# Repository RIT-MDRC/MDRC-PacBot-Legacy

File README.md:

# MDRC-PacBot
RIT MDRC's robot competing in Harvard's Pacbot Competition.

## Hardware

# What you need

1. A Raspberry Pi 4b
2. An Arduino Uno
3. A USB-B to USB-A adapter
4. Adafruit Motor Shield v2
5. USC-C to USB-A cable for powering the Raspberry Pi
6. 5 distance sensors (Sharp 0A51SK F 02)
7. The Pacbot shell
8. Motors (2x DC motors, 30:1 Micro Metal Gearmotor LP 6V with Extended Motor Shaft (Item #2202))
9. 2 Wheels
10. 1 caster wheel
11. Code from MDRC pacbot repo (https://github.com/RIT-MDRC/MDRC-PacBot.git)

# How to build the robot

1. Put the distance sensors in the holes of the Pacbot shell.
2. Plug the motor shield into the Arduino.
3. Ensure the microSD card is inserted into the Raspberry Pi.
4. Plug the raspberry pi into a power source using the USB-C to A cord.
5. Plug the arduino into the Raspberry Pi using the USB-A to USB-B cable.
6. Plug the motors into the motor shield using the M1 and M2 slots.
7. Plug the power wires of the sensors (red + black) into the 5v power of the motor shield
8. Plug the data wire (white) into the analog input of the motor shield.
9. Put the wheels on the motor axles.
10. Plug the 9V battery into the motor shield using the 5-12V wire slots.
11. SSH into the raspberry pi: `ssh pi@mdrcpi4.student.rit.edu`
12. Run ls /dev/tty* to find the serial port of the Arduino (similar to "USB0").
13. Locate motorControllerPassthrough.py and run it on the Raspberry Pi with the argument of /dev/tty/USB0 (replace with serial port).
14. On your computer, locate motorControllerPassthroughClient.py and run it: `python3 motorControllerPassthroughClient.py ws://mdrcpi4.student.rit.edu:8765`
15. Type "f", "b", "l", "r", or "s" (stop) to control the robot, or "q" to quit the program.

To learn more about the software, see the doc in the MDRC google drive https://docs.google.com/document/d/10UM2JkGd73kfUx4oTEAEH53nK31bbPSw4fjkly4F9ZI/edit

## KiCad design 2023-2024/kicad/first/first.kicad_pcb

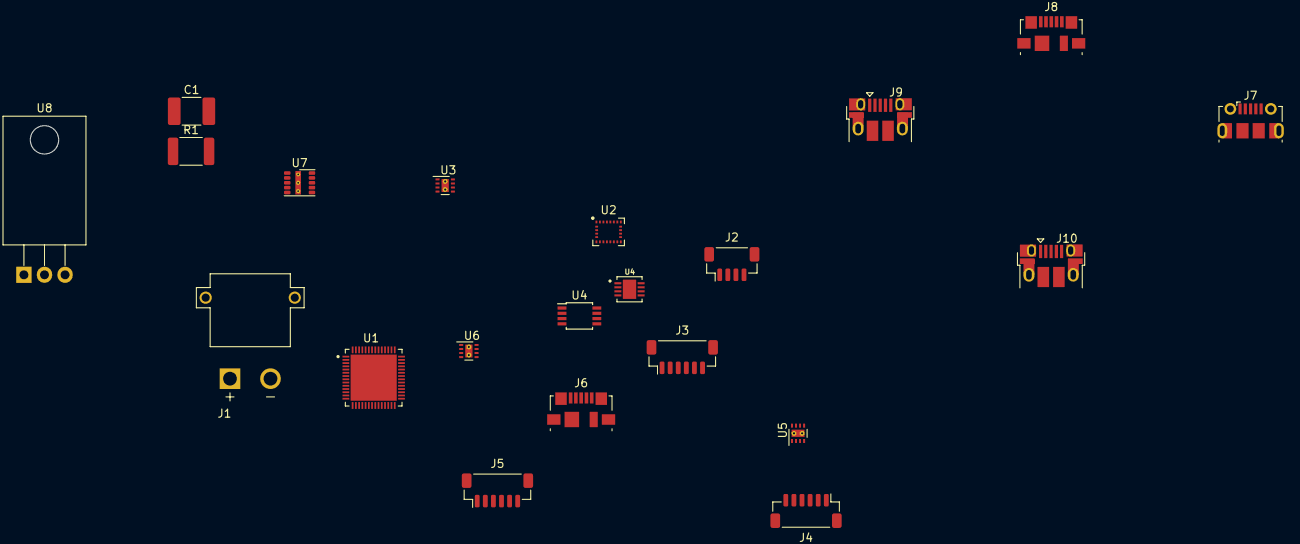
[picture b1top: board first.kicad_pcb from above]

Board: 2 copper layers, 21 parts (0 on the bottom side), 13 nets, no tracks yet.

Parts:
C1: 1u; C_1812_4532Metric_Pad1.57x3.40mm_HandSolder
J1: XT30PW-M; AMASS_XT30PW-M
J2: Conn_01x04; JST_SH_BM04B-SRSS-TB_1x04-1MP_P1.00mm_Vertical
J3, J4, J5: Conn_01x06; JST_SH_BM06B-SRSS-TB_1x06-1MP_P1.00mm_Vertical
J6, J8: USB_B_Micro; USB_Micro-B_Molex_47346-0001
J7: USB_B_Micro; USB_Micro-B_Molex-105017-0001
J9, J10: USB_B_Micro; USB_Micro-B_Amphenol_10103594-0001LF_Horizontal
R1: 50m; R_1812_4532Metric_Pad1.30x3.40mm_HandSolder
U1: ESP32-S3FH4R2; QFN40P700X700X90-57N
U2: LSM9DS1; LGA-24L_3x3.5mm_P0.43mm
U3, U5, U6: DRV8212P; WSON-8-1EP_2x2mm_P0.5mm_EP0.9x1.6mm_ThermalVias
U4: LTC2943IDD_PBF; SON50P300X300X80-9N
U4#2: DS2745U; TSSOP-8_3x3mm_P0.65mm
U7: LMZM23601V3; Texas_SIL0010A_MicroSiP-10-1EP_3.8x3mm_P0.6mm_EP0.7x2.9mm_T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
U8: LM7806_TO220; TO-220-3_Horizontal_TabDown

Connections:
+3.3V: J2.3, J3.3, J4.3, J5.3, U2.1 (VDDIO), U2.3 (VDDIO), U2.22 (VDD), U2.23 (VDD), U3.8 (VCC), U5.8 (VCC), U6.8 (VCC), U7.6 (VOUT), U7.7 (FB)
+6V: U3.1 (VM), U5.1 (VM), U6.1 (VM), U7.3 (VIN), U7.4 (EN), U8.3 (VO)
GND: C1.1, J1.N, J2.4, J3.6, J4.6, J5.6, J6.5 (GND), U1.57 (GND), U2.19 (GND), U2.20 (GND), U3.4 (GND), U3.9 (GND), U4.2 (GND), U4.3 (GND), U4.7 (GND), U4.9 (EXP), U5.4 (GND), U5.9 (GND), U6.4 (GND), U6.9 (GND), U7.1 (GND), U7.11 (GND), U8.2 (GND)
unnamed: J3.1, U6.2 (OUT1)
unnamed: J3.2, U6.3 (OUT2)
unnamed: J4.1, U5.2 (OUT1)
unnamed: J4.2, U5.3 (OUT2)
unnamed: J5.1, U3.2 (OUT1)
unnamed: J5.2, U3.3 (OUT2)
unnamed: U1.2 (VDD3P3), U1.3 (VDD3P3)
unnamed: U1.55 (VDDA), U1.56 (VDDA)
unnamed: C1.2, R1.1, U4.1 (SENSE+), U8.1 (VI)
unnamed: J1.P, R1.2, U4.8 (SENSE-)

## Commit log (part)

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2019-01-29 Meeting update
2019-01-29 addition of a subscription to fullstate into pacneat
2019-02-09 Pacneat can now restart and run the game still errors though
2019-02-12 changed hard
2019-02-23 cleaned up protoAI
2019-03-18 direction
2019-03-19 Changed the address of the highlevelpacman and pacbotcommsmodule using the pis ip address to talk to appear to the server.
2019-03-23 Using RPI
2019-03-23 4 GPIO output config
2019-03-23 Bug fix
2019-03-26 Sensor usage
2019-03-30 PID installation and usage
2019-03-30 ATUNE fix
2019-03-30 goes straight
2019-03-31 more changes
2019-04-03 Initial test of gyro+sensor to turn
2019-04-04 fixed warnings
2019-04-05 changed pins
2019-04-06 small change
2019-04-06 Failsafe randome function works
2019-09-22 Add .gitignore for __pycache__/ and .vscode/ directories
2019-09-23 Stop using the Queue wrapper for collections.deque
    I profiled this, and the Queue wrapper was introducing
    measurable overhead. It's a bit faster just using an
    unwrapped collections.deque.
    I also did some minor, non-functional reformatting.
2019-09-24 Refactor findPath and breadth_first_search control flow
    Use a loop instead of recursion. This is a little faster and
    (in my opinion) more readable.
2019-09-28 Write new optimized_search module
    It uses a precomputed lookup table of distances & directions
    between intersections for very fast distance/direction lookup
    between any two tiles.
    The file preprocess_grid.py generates the lookup tables.
2019-09-28 Comment out GPIO stuff
    So it runs on my laptop
2019-09-28 Print some debug/timing information each tick
2019-09-28 Update find_closest_ghosts to use the new optimized search
2019-09-28 Add .DS_store to the .gitignore
2019-09-28 copied update from 2018
2019-09-28 Created lowlevel folder
2019-10-08 Added headers for lowlevel modules
2020-01-30 -Add logic for motor controller
    -Create wrapper for distance sensor
2020-02-10 Fix some semantic errors
2021-09-19 Changed IP addresses to localhost, added two shell files for use when running on Linux
2021-09-19 Added gitpull.sh to /2021-2022/linux to make it faster to pull to the raspian systems
2021-09-25 + Print the score at each tick
2021-09-25 + Added intermediary print statement for time complexity analysis
2021-09-25 + Fixed directories in pacbotNoVisToFile.sh
2021-09-25 + Added .gitignore to ignore test results + Added line in pacbotNoVisToFile.sh to make the test directory if it doesn't exist
2021-09-25 changed sleep duration from 1 to 0.6s
2021-09-25 changed sleep duration back to 1 second
2021-10-02 + Edited pacbotNoVisToFile.sh to actually start the simulation - it works now as a bash file
2021-10-02 + New sh file path in testweights.py / sleep 5 in testweights.sh to see errors
2021-10-02 channgef heursitic to 1 for super pellsts
2021-10-02 + Fixed file path in testweights.py (again)
2021-10-02 Added a text file that contains the weights of our code used to test for the best combination
2021-10-02 added .split to line 29
2021-10-02 Added loop to read lines in test_weights.txt
2021-10-02 type casted to int on lines 30-35
2021-10-02 Changed frquency to 2 in weighs.txt
2021-10-11 Updates test_weights.txt to match weights.txt, updated testweights.py to use subprocess.Popen instead of subprocess.call because Popen can accept stdin and use stdout
2021-10-11 Updates test_weights.txt to add more iterations, updated testweights.py to kill process when it says "stop" (when pacbot dies) and print out the score for each iteration
2021-10-11 pacbotNoVisToFile.sh now again puts GameEngine output to file, but python script is switched to pacbotNoVis to capture all stdout testweights.py includes a check so that it does not try to do empty l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
2021-10-11 Uses terminate instead of kill, converts binary string using decode
2021-10-11 Forced input to pacbotNoVis.sh
2021-10-11 Fixed command not in list form
2021-10-11 List form command
2021-10-11 Print output from program
2021-10-11 testweights.py now starts all other python processes without the use of the sh file. js file was deleted because this os cannot run node
2021-10-11 Reformat game engine initialization
2021-10-11 Added processes created print and ignored gameEngine output
2021-10-11 Terminate instead of kill
2021-10-11 Print score as int, do all iterations
2021-10-11 Only 1 weights set, also output results to git ignored file
2021-10-11 Added second weights set
2021-10-11 Run only the first iteration - next ones will be run in subsequent processes so that the ports can be released
2021-10-11 Script starts new independent process when finished so that ports can be reopened
2021-10-11 Prints which weight set it is on
2021-10-11 Program waits for Pacman to die before quitting each iteration
2021-10-11 Changed conflicting variable names
2021-10-11 Fixed while loop
2021-10-11 Looking for multiple consecutive stops because sometimes pacman stops on his own
2021-10-13 Made pacbot process nohup in hopes of remerging testweights into single process
2021-10-14 Kill didn't work either, reverting last two commits (terminate instead of kill, no nohup for pacbot progress).
2021-10-14 Fixed shV2 file, removed wait time at the beginning of python script
2021-10-14 Fixed file path when checking if process complete
2021-10-14 Removed infinite while loop
2021-10-14 Fixed for loop... not ending... again....
2021-10-14 Print sys.argv to see what it looks like
2021-10-14 Fixed variable names in pacbotCommsModule.py
2021-10-14 Test with 100 equal weight sets, decreased time between initializations to 0.5 seconds
2021-10-14 Checks ports before attempting to launch games on them in an effort to reduce collisions (estimated 29% of ports collided last time)
2021-10-14 Increased delay between servers start and clients start to ensure servers start up before clients try to connect (should fix errno111)
2021-10-14 Added check so that we don't disqualify programs that had a laggy start
2021-10-16 testweights v2
2021-10-30 testweights 0.7
2021-10-31 Added testweightsV3.py which posts its scores to a google sheet
2021-10-31 Removed hardcoded test
2021-10-31 Increased delay after process initializing
2021-10-31 Removed delay after initializing processes, added try/catch for result file
2021-10-31 Hardcoded dashboard information for testing, rate limit per minute exceeded
2021-10-31 Fixed hardcoded values... again...
2021-10-31 Fixed completedProcesses not being a dictionary
2021-10-31 Added try/catch loops to try to avoid the program failing
2021-10-31 Prints length of processes - program is using too much memory
2021-10-31 Fixed length of processes printing
2021-10-31 Change to only one call for dashboard data instead of three
2021-11-01 Kill instead of terminate - processes aren't dying and are taking up memory
2021-11-01 Added ls to see where python program is running from
2021-11-01 Added (cd ../;) to highLevelPacman call so that it is started from the correct root folder
2021-11-01 Added printing process exception
2021-11-01 Removed (cd ../) because it doesn't work with popen
2021-11-01 Use cwd= instead of (cd../;)
2021-11-01 added , stdout=subprocess.DEVNULL to popen calls to not get STOP STOP STOP constantly in stdout
2021-11-01 changed if to while.... WOW that code hasn't done anything since I wrote it because it shouldn't have worked
2021-11-01 print socket error nums
2021-11-01 fixed more descriptive prints
2021-11-01 try commenting out port finder
2021-11-01 increase wait time before commsmodule is initiated
2021-11-01 added process.wait() after terminate (x2)
2021-11-01 rewrote testweightsV3.py intended to be run once but takes from google sheet
2021-11-01 added print statements
2021-11-01 fixed weight storing as list
2021-11-01 use only one process per weight set instead of 6 (using v2)
2021-11-01 fixed weight set indexing
2021-11-01 waits for ports to close on previous process
2021-11-20 made a copy of the highLevelPackman.py file before making some changes to super pellet behavior.
2022-01-22 Horde Changes 1/22/22
2022-02-05 Works with multithreading
2022-02-12 Synchronous
2022-02-12 Data analysis
2022-02-26 Additional weights
2022-02-27 Optimize for median score instead of mean score
2022-03-26 Create motorControl.ino
    Arduino code file
2022-04-02 add motor controller passthrough scripts
2022-04-02 Fix bug with argument in motorControllerPassthrough.py
2022-04-02 Added awaits
2022-04-02 Added loop for motorControllerPassthrough.py
2022-04-02 Print output from serial
2022-04-02 print more outputs from serial
2022-04-16 add google doc to readme
2022-04-16 More data analysis & param optimization work
2022-09-10 Update README.md with some explicit commands
2022-10-17 Initial code to send sensor values from Arduino
2022-11-05 Implement raycasting
2023-01-28 Add function stubs
2023-01-28 Remove grid from function arguments
2023-01-28 fixed naming issue
2023-01-28 added TODO
2023-01-28 - Calculate open grid spaces list at the beginning of the program - implement pf_random_point
2023-01-28 refactoring
2023-02-04 implemented pure_pursuit into simulator
2023-02-11 Basic BFS pathfinding (broken import)
2023-02-11 integrated simple bfs finder with pure pursuit
2023-02-11 Fix BFS path making
2023-02-11 Flip screen so that up is positive
2023-02-11 removed redundant points
2023-02-18 minor speed changes
2023-02-18 Add some ghost code
2023-04-07 Add README with submodule directions
2023-04-07 Rename submodule correctly
2023-04-07 AutoRobo client, requirements
2023-04-07 AutoRobo server can now run each component
2023-04-07 Supports recording and playing back games
2023-04-07 Improve UI and file organization
2023-04-08 Low level code: encoder feedback and reading IR sensor data. TO BE TESTED
2023-04-08 Set up stuff that will run on the raspberry pi
2023-04-15 newline fixes
2023-04-15 fixed encoders
2023-04-15 Set up rust <-> python
2023-04-22 changed arduino packets to use encoder deltas
2023-04-22 Set up default position for test Add ghost frightened counter Add environment variables for USE_PROJECTOR and USE_REAL_ARDUINO
2023-04-22 Set up default position for test Add env var for max wheel speed Fix grid
2023-04-22 Draw all PF points
2023-04-22 Fix possibly-broken distance_to_voltage function
2023-04-22 Client now receives data from server
2023-04-26 Change sense pin from A4 to A5
2023-04-27 add experimental sensor lines
2023-04-27 server readme info
2023-04-27 git packages
2023-04-28 reorganize files, fix a ton of stuff, robot can now drive in simulation
2023-04-28 update particle filter using location from projector
2023-04-28 add forced option
2023-04-28 motors working
2023-04-29 reverse angles so that high angles are to the left
2023-04-29 motor control improvements
2023-04-29 turn off sensor lines in visualization
2023-04-29 Competition settings
2023-05-30 Create project for new 2023-2024 organization, for code for the arduino
2023-05-30 Separate model and service
2023-06-05 Initialize typescript/bootstrap project
2023-06-05 Minimum working Konva example
2023-06-06 we using vue now
2023-06-06 Install vuetify
2023-06-16 Remove non-existing derived traits
2023-06-16 Add serial manager arduino-independent logic to ensure safe message sending
2023-06-17 Add serial communication with Arduino
2023-06-17 Resolve warnings, add LED command
2023-06-17 Add messages for distance sensors, encoders, and motors
2023-06-17 Documentation
2023-06-22 add svelte project
2023-06-22 Add Material Typoography
2023-06-23 vue konva
2023-06-23 Don't make buttons that delete themselves
2023-06-23 force dragging to change width even when it causes bugs
2023-06-23 improve settings panel
2023-06-27 add websocket client to frontend
2023-06-27 Change websocket to use log4rs instead of println
2023-06-27 add ability to blast message to all current clients
2023-06-27 minimal documentation
2023-07-08 Add test service WIP
2023-07-11 Support service statuses
2023-07-11 Preperation for web communication
